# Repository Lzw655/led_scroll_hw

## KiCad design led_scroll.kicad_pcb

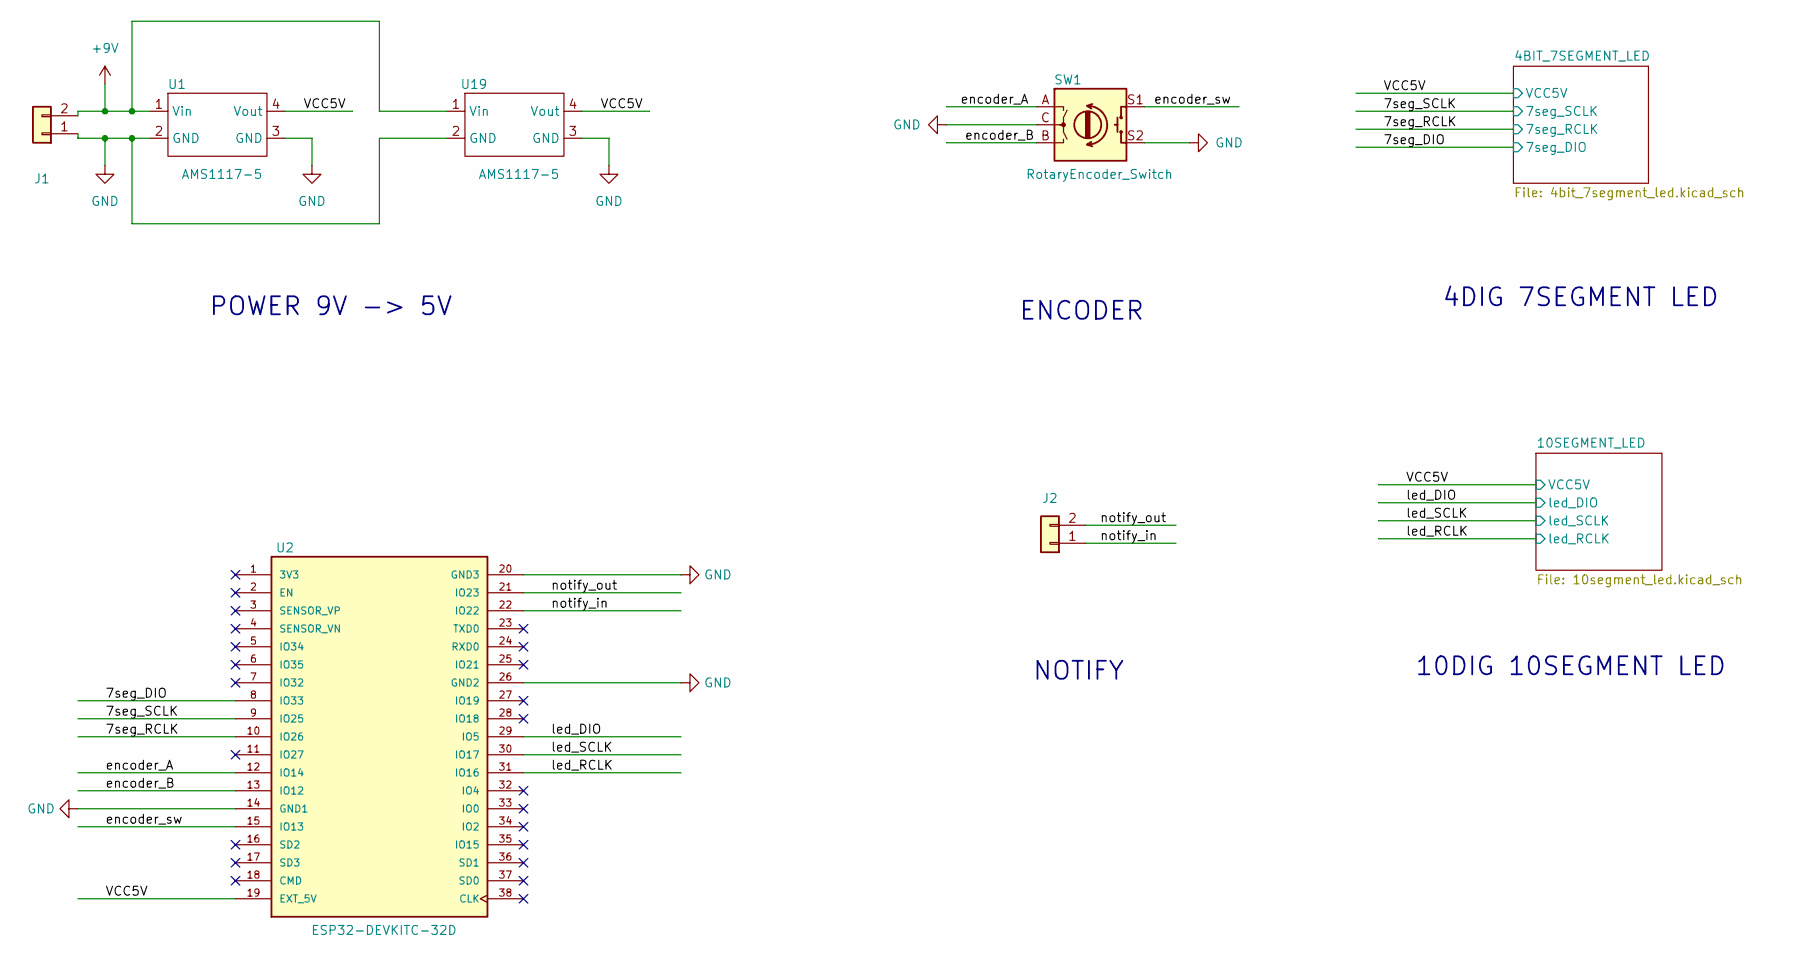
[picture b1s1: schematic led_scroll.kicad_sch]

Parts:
J1, J2: KF128_5.08_2P
SW1: RotaryEncoder_Switch; RotaryEncoder_Alps_EC11E-Switch_Vertical_H20mm
U1, U19: AMS1117-5; AMS1117
U2: ESP32-DEVKITC-32D; PARTREV 4

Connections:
+9V: J1.2, U1.1 (Vin), U19.1 (Vin)
/7seg_DIO: U2.8 (IO33); also elsewhere on the board
/7seg_RCLK: U2.10 (IO26); also elsewhere on the board
/7seg_SCLK: U2.9 (IO25); also elsewhere on the board
/VCC5V: U1.4 (Vout), U2.19 (EXT_5V), U19.4 (Vout); also elsewhere on the board
/encoder_A: SW1.A, U2.12 (IO14)
/encoder_B: SW1.B, U2.13 (IO12)
/encoder_sw: SW1.S1, U2.15 (IO13)
/led_DIO: U2.29 (IO5); also elsewhere on the board
/led_RCLK: U2.31 (IO16); also elsewhere on the board
/led_SCLK: U2.30 (IO17); also elsewhere on the board
/notify_in: J2.1, U2.22 (IO22)
/notify_out: J2.2, U2.21 (IO23)
GND: J1.1, SW1.C, SW1.S2, U1.2 (GND), U1.3 (GND), U2.14 (GND1), U2.20 (GND3), U2.26 (GND2), U19.2 (GND), U19.3 (GND); also elsewhere on the board

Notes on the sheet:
NOTIFY
POWER 9V -> 5V
ENCODER
10DIG 10SEGMENT LED
4DIG 7SEGMENT LED

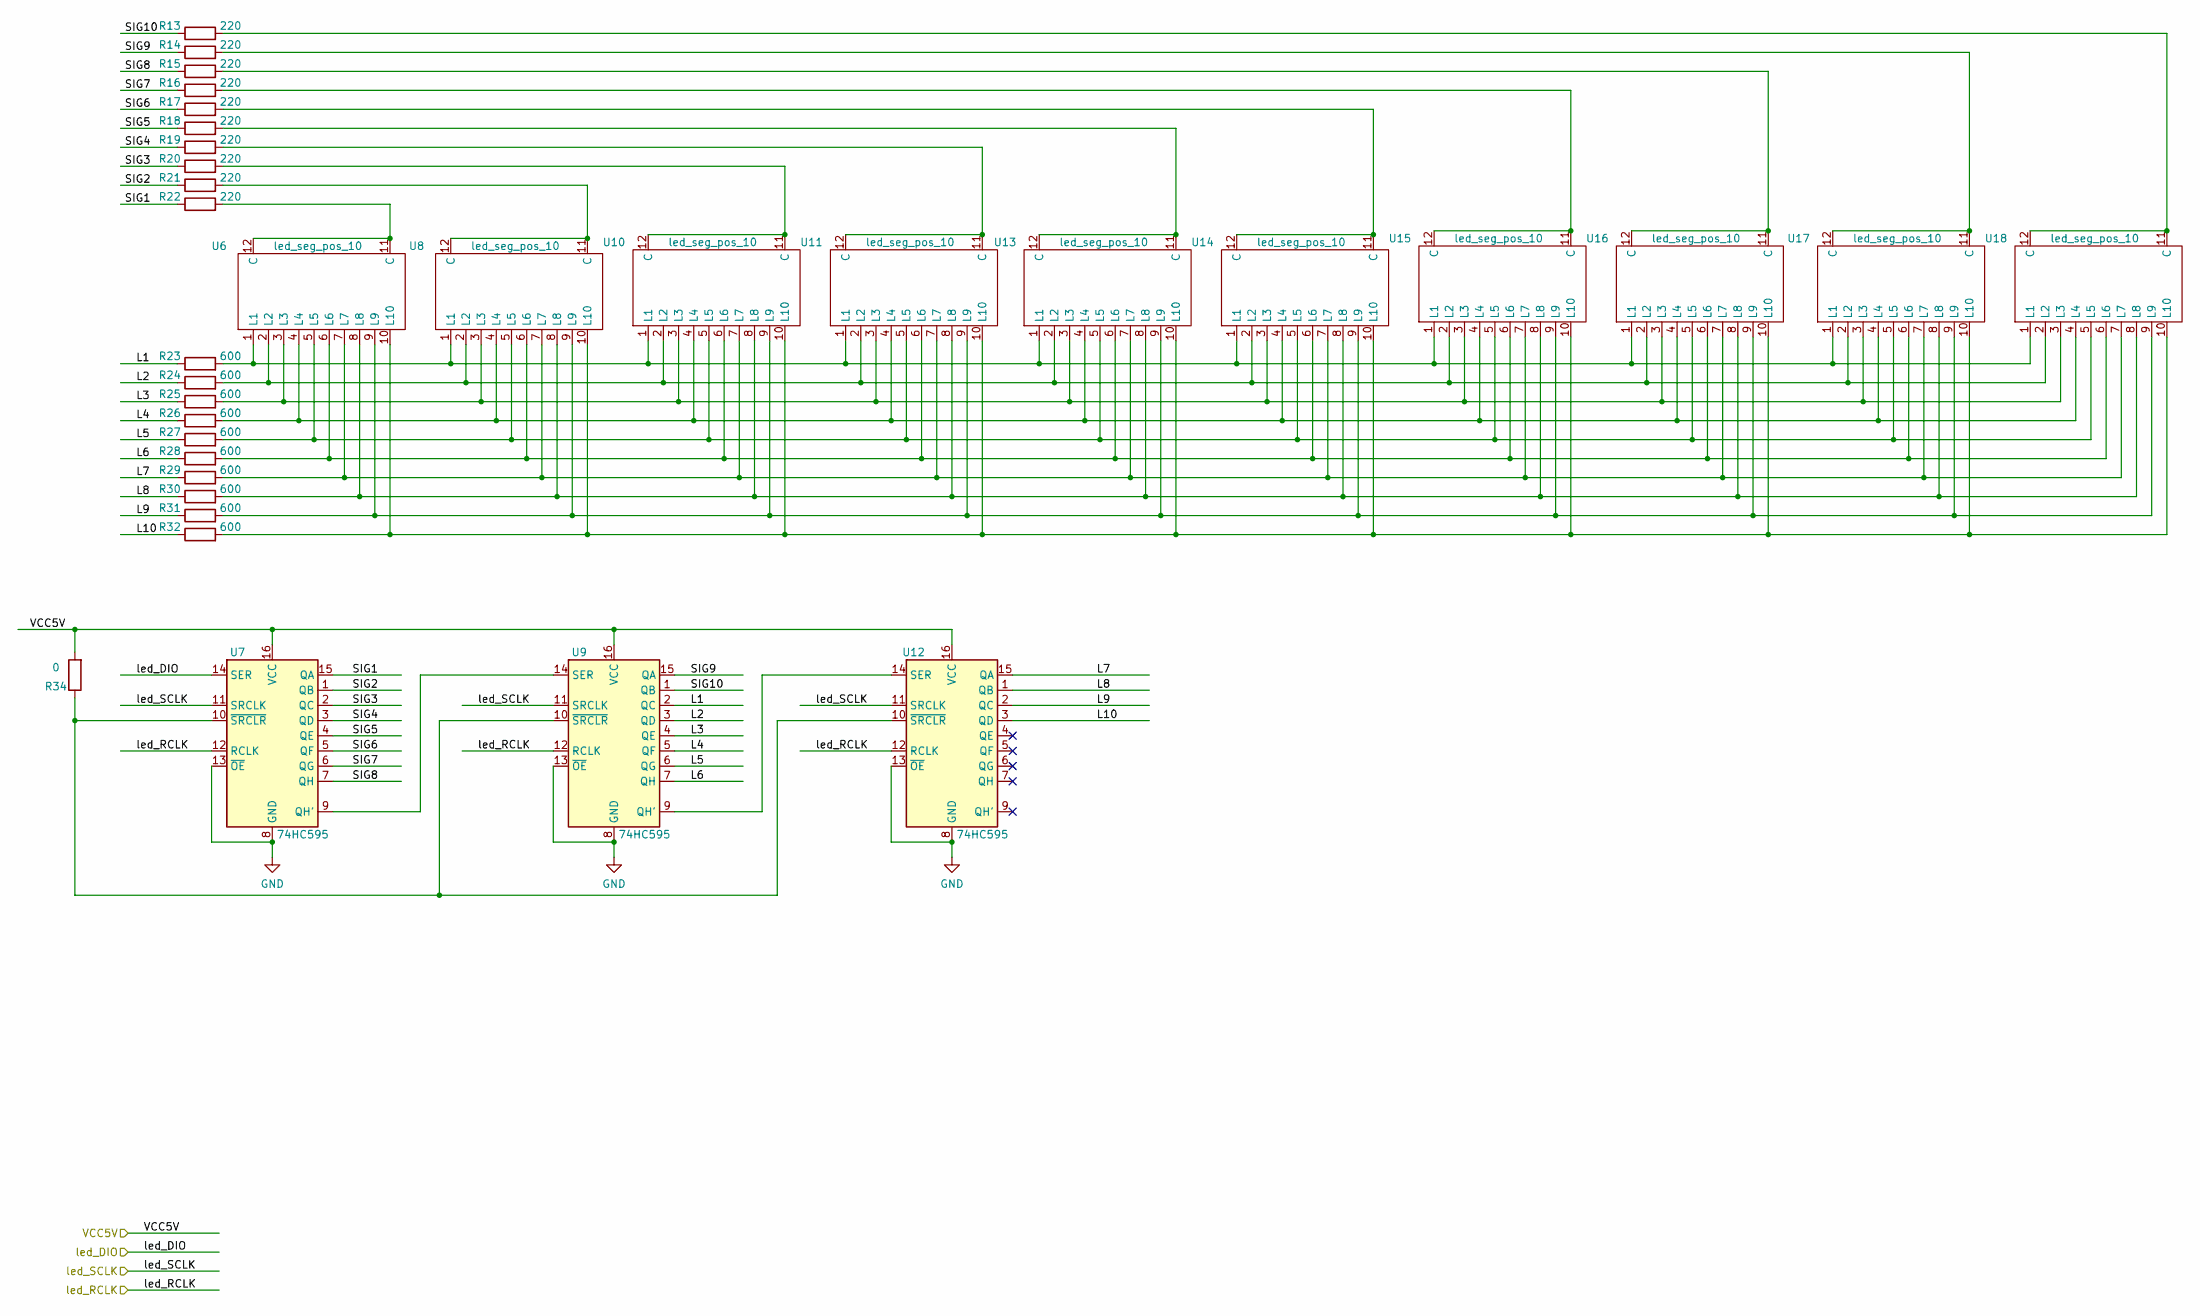
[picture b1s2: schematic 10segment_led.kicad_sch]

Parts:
R13, R14, R15, R16, R17, R18, R19, R20, R21, R22: 220; R_0603_1608Metric
R23, R24, R25, R26, R27, R28, R29, R30, R31, R32: 600; R_0603_1608Metric
R34: 0; R_0603_1608Metric
U6, U8, U10, U11, U13, U14, U15, U16, U17, U18: led_seg_pos_10; led_seg_2.54_10
U7, U9, U12: 74HC595; SOIC-16_3.9x9.9mm_P1.27mm

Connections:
/10SEGMENT_LED/L1: R23.1, U9.2 (QC)
/10SEGMENT_LED/L2: R24.1, U9.3 (QD)
/10SEGMENT_LED/L3: R25.1, U9.4 (QE)
/10SEGMENT_LED/L4: R26.1, U9.5 (QF)
/10SEGMENT_LED/L5: R27.1, U9.6 (QG)
/10SEGMENT_LED/L6: R28.1, U9.7 (QH)
/10SEGMENT_LED/L7: R29.1, U12.15 (QA)
/10SEGMENT_LED/L8: R30.1, U12.1 (QB)
/10SEGMENT_LED/L9: R31.1, U12.2 (QC)
/10SEGMENT_LED/L10: R32.1, U12.3 (QD)
/10SEGMENT_LED/SIG1: R22.1, U7.15 (QA)
/10SEGMENT_LED/SIG2: R21.1, U7.1 (QB)
/10SEGMENT_LED/SIG3: R20.1, U7.2 (QC)
/10SEGMENT_LED/SIG4: R19.1, U7.3 (QD)
/10SEGMENT_LED/SIG5: R18.1, U7.4 (QE)
/10SEGMENT_LED/SIG6: R17.1, U7.5 (QF)
/10SEGMENT_LED/SIG7: R16.1, U7.6 (QG)
/10SEGMENT_LED/SIG8: R15.1, U7.7 (QH)
/10SEGMENT_LED/SIG9: R14.1, U9.15 (QA)
/10SEGMENT_LED/SIG10: R13.1, U9.1 (QB)
/VCC5V: R34.2, U7.16 (VCC), U9.16 (VCC), U12.16 (VCC); also elsewhere on the board
/led_DIO: U7.14 (SER); also elsewhere on the board
/led_RCLK: U7.12 (RCLK), U9.12 (RCLK), U12.12 (RCLK); also elsewhere on the board
/led_SCLK: U7.11 (SRCLK), U9.11 (SRCLK), U12.11 (SRCLK); also elsewhere on the board
GND: U7.8 (GND), U7.13 (~OE), U9.8 (GND), U9.13 (~OE), U12.8 (GND), U12.13 (~OE); also elsewhere on the board
unnamed: R13.2, U18.11 (C), U18.12 (C)
unnamed: R14.2, U17.11 (C), U17.12 (C)
unnamed: R15.2, U16.11 (C), U16.12 (C)
unnamed: R16.2, U15.11 (C), U15.12 (C)
unnamed: R17.2, U14.11 (C), U14.12 (C)
unnamed: R18.2, U13.11 (C), U13.12 (C)
unnamed: R19.2, U11.11 (C), U11.12 (C)
unnamed: R20.2, U10.11 (C), U10.12 (C)
unnamed: R21.2, U8.11 (C), U8.12 (C)
unnamed: R22.2, U6.11 (C), U6.12 (C)
unnamed: R23.2, U6.1 (L1), U8.1 (L1), U10.1 (L1), U11.1 (L1), U13.1 (L1), U14.1 (L1), U15.1 (L1), U16.1 (L1), U17.1 (L1), U18.1 (L1)
unnamed: R24.2, U6.2 (L2), U8.2 (L2), U10.2 (L2), U11.2 (L2), U13.2 (L2), U14.2 (L2), U15.2 (L2), U16.2 (L2), U17.2 (L2), U18.2 (L2)
unnamed: R25.2, U6.3 (L3), U8.3 (L3), U10.3 (L3), U11.3 (L3), U13.3 (L3), U14.3 (L3), U15.3 (L3), U16.3 (L3), U17.3 (L3), U18.3 (L3)
unnamed: R26.2, U6.4 (L4), U8.4 (L4), U10.4 (L4), U11.4 (L4), U13.4 (L4), U14.4 (L4), U15.4 (L4), U16.4 (L4), U17.4 (L4), U18.4 (L4)
unnamed: R27.2, U6.5 (L5), U8.5 (L5), U10.5 (L5), U11.5 (L5), U13.5 (L5), U14.5 (L5), U15.5 (L5), U16.5 (L5), U17.5 (L5), U18.5 (L5)
unnamed: R28.2, U6.6 (L6), U8.6 (L6), U10.6 (L6), U11.6 (L6), U13.6 (L6), U14.6 (L6), U15.6 (L6), U16.6 (L6), U17.6 (L6), U18.6 (L6)
unnamed: R29.2, U6.7 (L7), U8.7 (L7), U10.7 (L7), U11.7 (L7), U13.7 (L7), U14.7 (L7), U15.7 (L7), U16.7 (L7), U17.7 (L7), U18.7 (L7)
unnamed: R30.2, U6.8 (L8), U8.8 (L8), U10.8 (L8), U11.8 (L8), U13.8 (L8), U14.8 (L8), U15.8 (L8), U16.8 (L8), U17.8 (L8), U18.8 (L8)
unnamed: R31.2, U6.9 (L9), U8.9 (L9), U10.9 (L9), U11.9 (L9), U13.9 (L9), U14.9 (L9), U15.9 (L9), U16.9 (L9), U17.9 (L9), U18.9 (L9)
unnamed: R32.2, U6.10 (L10), U8.10 (L10), U10.10 (L10), U11.10 (L10), U13.10 (L10), U14.10 (L10), U15.10 (L10), U16.10 (L10), U17.10 (L10), U18.10 (L10)
unnamed: R34.1, U7.10 (~SRCLR), U9.10 (~SRCLR), U12.10 (~SRCLR)
unnamed: U7.9 (QH'), U9.14 (SER)
unnamed: U9.9 (QH'), U12.14 (SER)

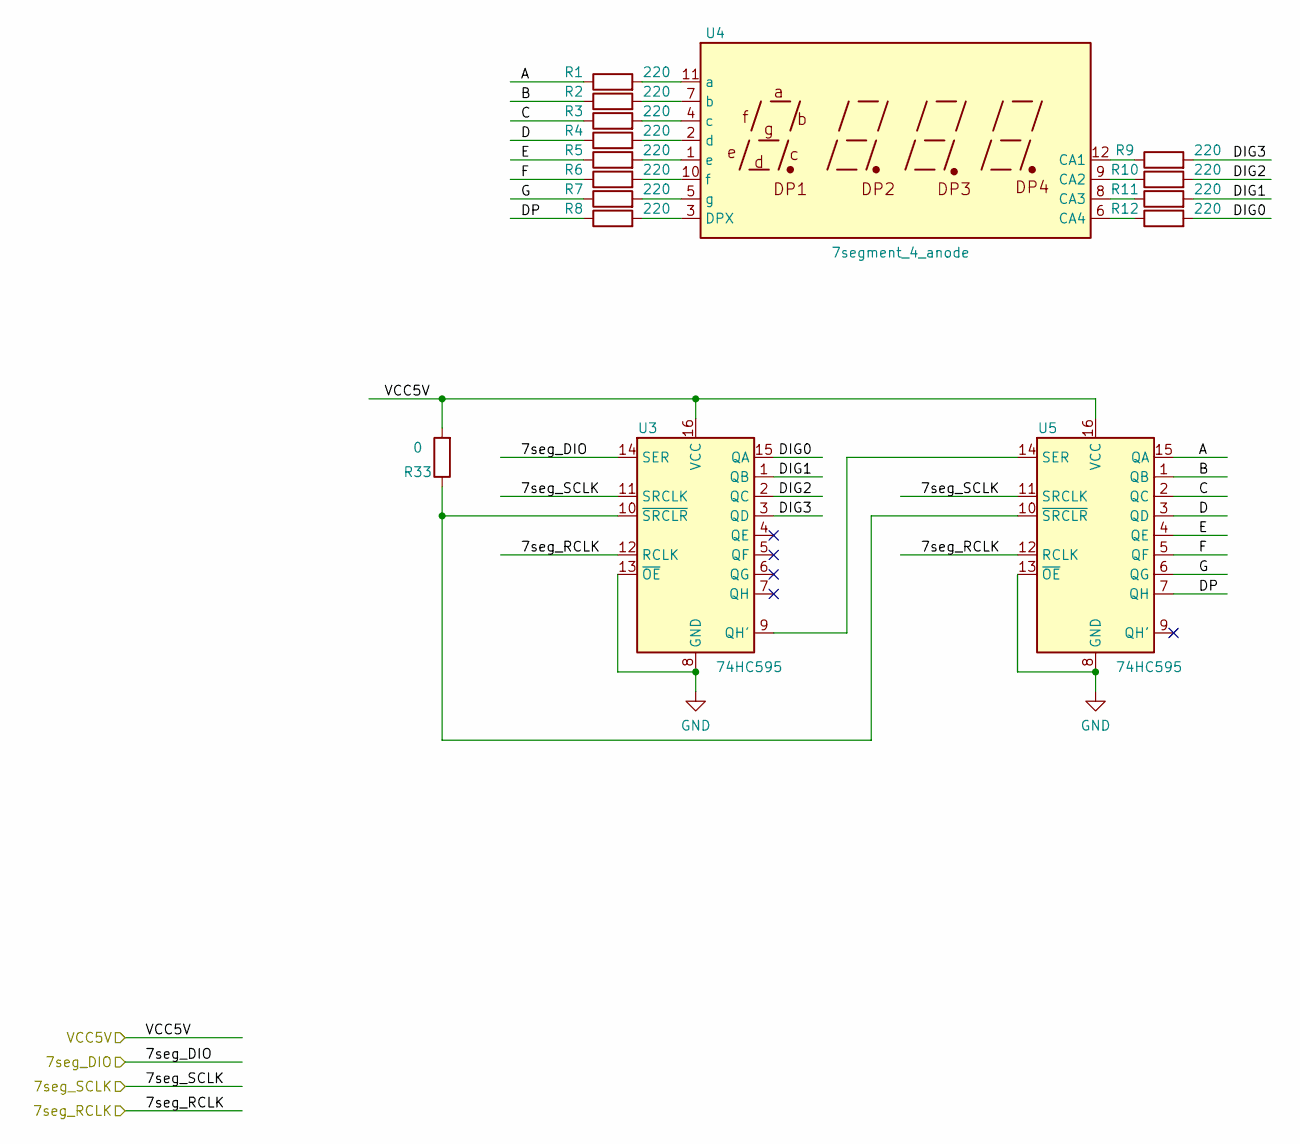
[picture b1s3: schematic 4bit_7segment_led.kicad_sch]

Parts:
R1, R2, R3, R4, R5, R6, R7, R8, R9, R10, R11, R12: 220; R_0603_1608Metric
R33: 0; R_0603_1608Metric
U3, U5: 74HC595; SOIC-16_3.9x9.9mm_P1.27mm
U4: 7segment_4_anode; 7segment_4_0.56

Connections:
/4BIT_7SEGMENT_LED/A: R1.1, U5.15 (QA)
/4BIT_7SEGMENT_LED/B: R2.1, U5.1 (QB)
/4BIT_7SEGMENT_LED/C: R3.1, U5.2 (QC)
/4BIT_7SEGMENT_LED/D: R4.1, U5.3 (QD)
/4BIT_7SEGMENT_LED/DIG0: R12.2, U3.15 (QA)
/4BIT_7SEGMENT_LED/DIG1: R11.2, U3.1 (QB)
/4BIT_7SEGMENT_LED/DIG2: R10.2, U3.2 (QC)
/4BIT_7SEGMENT_LED/DIG3: R9.2, U3.3 (QD)
/4BIT_7SEGMENT_LED/DP: R8.1, U5.7 (QH)
/4BIT_7SEGMENT_LED/E: R5.1, U5.4 (QE)
/4BIT_7SEGMENT_LED/F: R6.1, U5.5 (QF)
/4BIT_7SEGMENT_LED/G: R7.1, U5.6 (QG)
/7seg_DIO: U3.14 (SER); also elsewhere on the board
/7seg_RCLK: U3.12 (RCLK), U5.12 (RCLK); also elsewhere on the board
/7seg_SCLK: U3.11 (SRCLK), U5.11 (SRCLK); also elsewhere on the board
/VCC5V: R33.2, U3.16 (VCC), U5.16 (VCC); also elsewhere on the board
GND: U3.8 (GND), U3.13 (~OE), U5.8 (GND), U5.13 (~OE); also elsewhere on the board
unnamed: R1.2, U4.11 (a)
unnamed: R2.2, U4.7 (b)
unnamed: R3.2, U4.4 (c)
unnamed: R4.2, U4.2 (d)
unnamed: R5.2, U4.1 (e)
unnamed: R6.2, U4.10 (f)
unnamed: R7.2, U4.5 (g)
unnamed: R8.2, U4.3 (DPX)
unnamed: R9.1, U4.12 (CA1)
unnamed: R10.1, U4.9 (CA2)
unnamed: R11.1, U4.8 (CA3)
unnamed: R12.1, U4.6 (CA4)
unnamed: R33.1, U3.10 (~SRCLR), U5.10 (~SRCLR)
unnamed: U3.9 (QH'), U5.14 (SER)

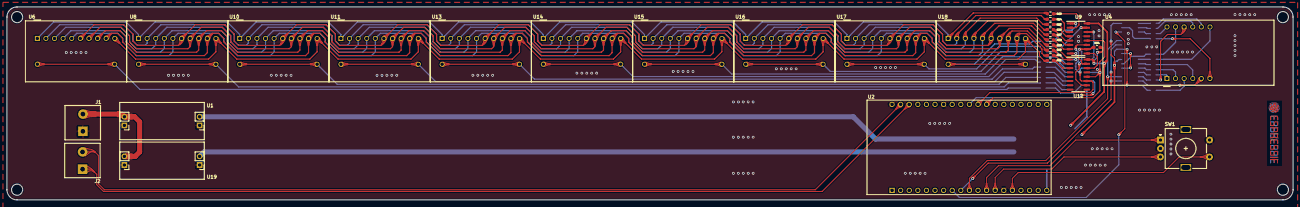
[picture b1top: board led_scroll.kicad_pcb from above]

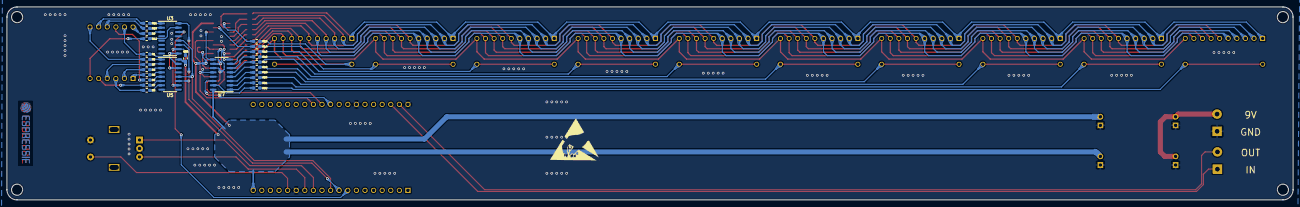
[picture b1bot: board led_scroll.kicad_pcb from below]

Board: 2 copper layers, 380.0 x 57.0 mm, 56 parts (26 on the bottom side), 83 nets.

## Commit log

2022-08-06 sch: finish
2022-08-14 modify packet of res
